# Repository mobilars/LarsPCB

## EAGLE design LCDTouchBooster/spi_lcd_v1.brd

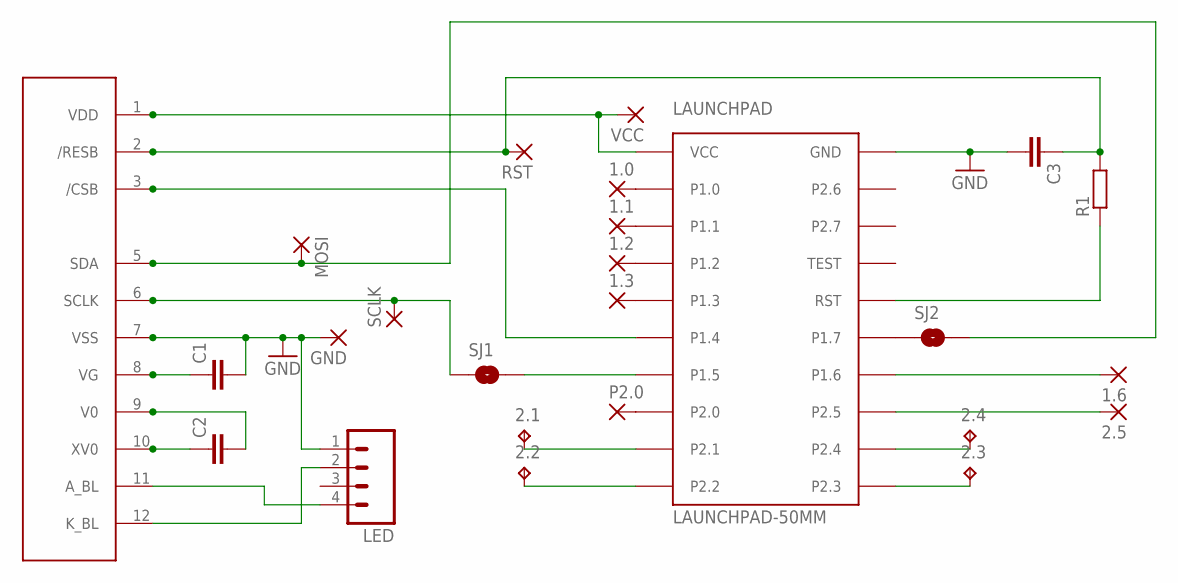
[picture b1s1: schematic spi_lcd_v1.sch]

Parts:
1.0, 1.1, 1.2, 1.3, 1.6, 2.5: 2,15/1,0
2.1, 2.2, 2.3, 2.4: TPTP07R; TP07R
C1, C2, C3: CAP1206; 1206
GND: 2,15/1,0
LAUNCHPAD: LAUNCHPAD-50MM
LED: M04PTH; 1X04
MOSI: 2,15/1,0
P2.0: 2,15/1,0
R1: R-EU_R1206; R1206
RST: 2,15/1,0
SCLK: 2,15/1,0
SJ1, SJ2: SOLDERJUMPERTRACE; SJ_2S-TRACE
U$1: PE9665WRFPE9665WRF-WHOLE; PE9665WRF
VCC: 2,15/1,0

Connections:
GND: C1.2, C3.2, GND.1, LAUNCHPAD.GND, LED.1, U$1.7 (VSS)
unnamed: C2.1, U$1.10 (XV0)
unnamed: C2.2, U$1.9 (V0)
unnamed: C1.1, U$1.8 (VG)
unnamed: 2.5.1, LAUNCHPAD.P2.5
unnamed: C3.1, R1.2, RST.1, U$1.2 (/RESB)
unnamed: 1.0.1, LAUNCHPAD.P1.0
unnamed: SCLK.1, SJ1.1, U$1.6 (SCLK)
unnamed: MOSI.1, SJ2.2, U$1.5 (SDA)
unnamed: LAUNCHPAD.P1.4, U$1.3 (/CSB)
unnamed: LAUNCHPAD.RST, R1.1
unnamed: 1.6.1, LAUNCHPAD.P1.6
unnamed: 1.2.1, LAUNCHPAD.P1.2
unnamed: 2.1.TP, LAUNCHPAD.P2.1
unnamed: 2.2.TP, LAUNCHPAD.P2.2
unnamed: 2.4.TP, LAUNCHPAD.P2.4
unnamed: 2.3.TP, LAUNCHPAD.P2.3
unnamed: 1.3.1, LAUNCHPAD.P1.3
unnamed: LAUNCHPAD.P2.0, P2.0.1
unnamed: 1.1.1, LAUNCHPAD.P1.1
unnamed: LAUNCHPAD.P1.7, SJ2.1
unnamed: LAUNCHPAD.P1.5, SJ1.2
unnamed: LED.2, U$1.12 (K_BL)
unnamed: LED.4, U$1.11 (A_BL)
VDD: LAUNCHPAD.VCC, U$1.1 (VDD), VCC.1

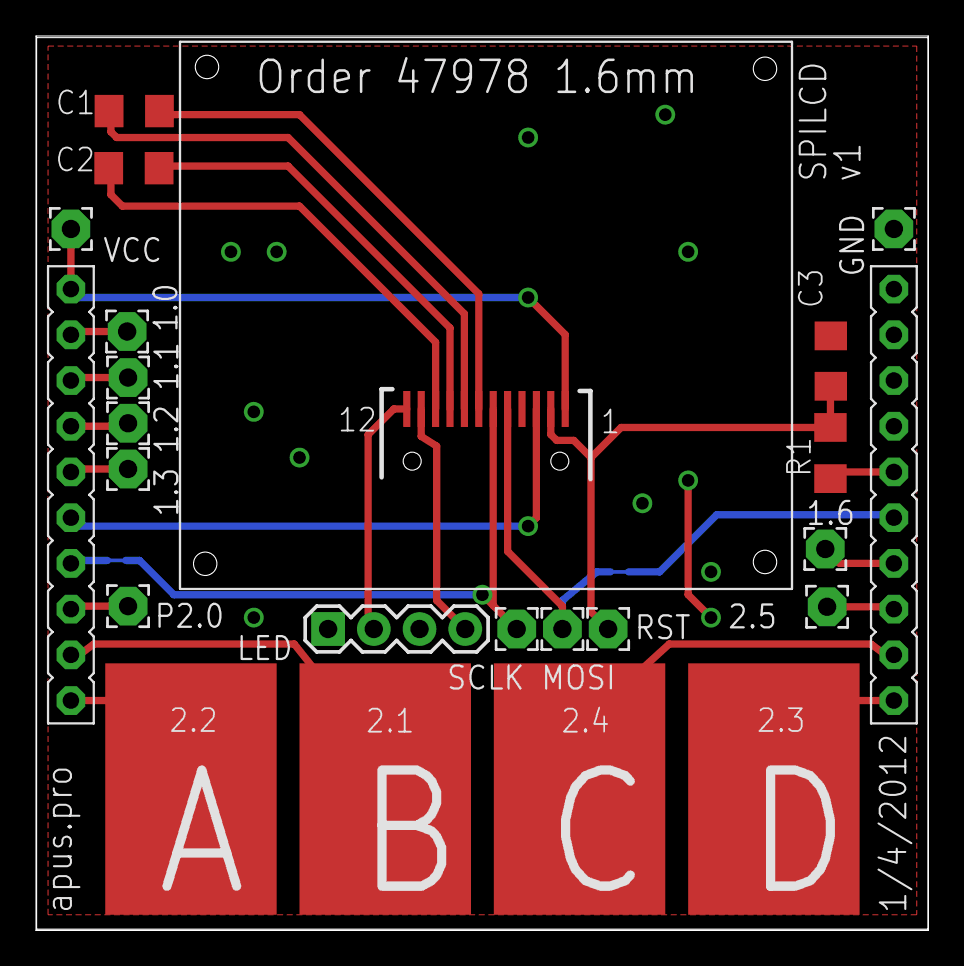
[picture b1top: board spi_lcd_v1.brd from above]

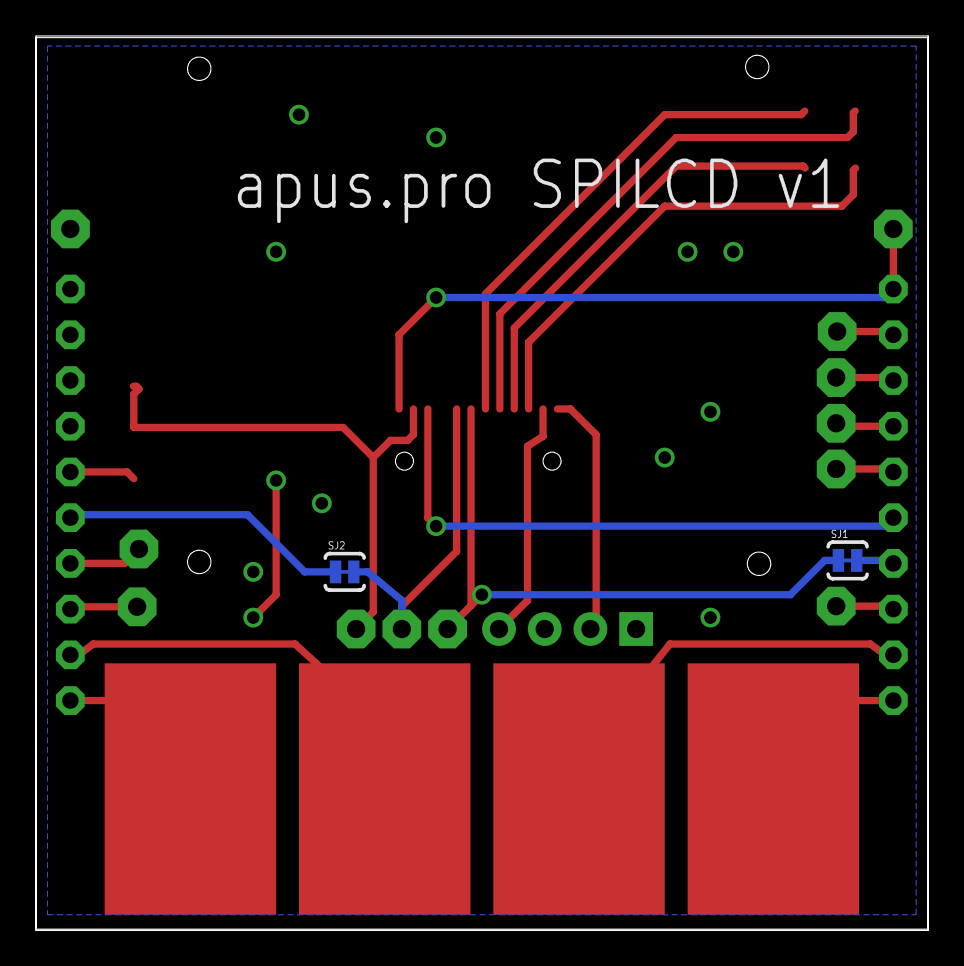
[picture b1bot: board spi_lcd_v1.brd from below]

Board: 2 copper layers, 49.6 x 49.7 mm, 25 parts (2 on the bottom side), 25 nets.

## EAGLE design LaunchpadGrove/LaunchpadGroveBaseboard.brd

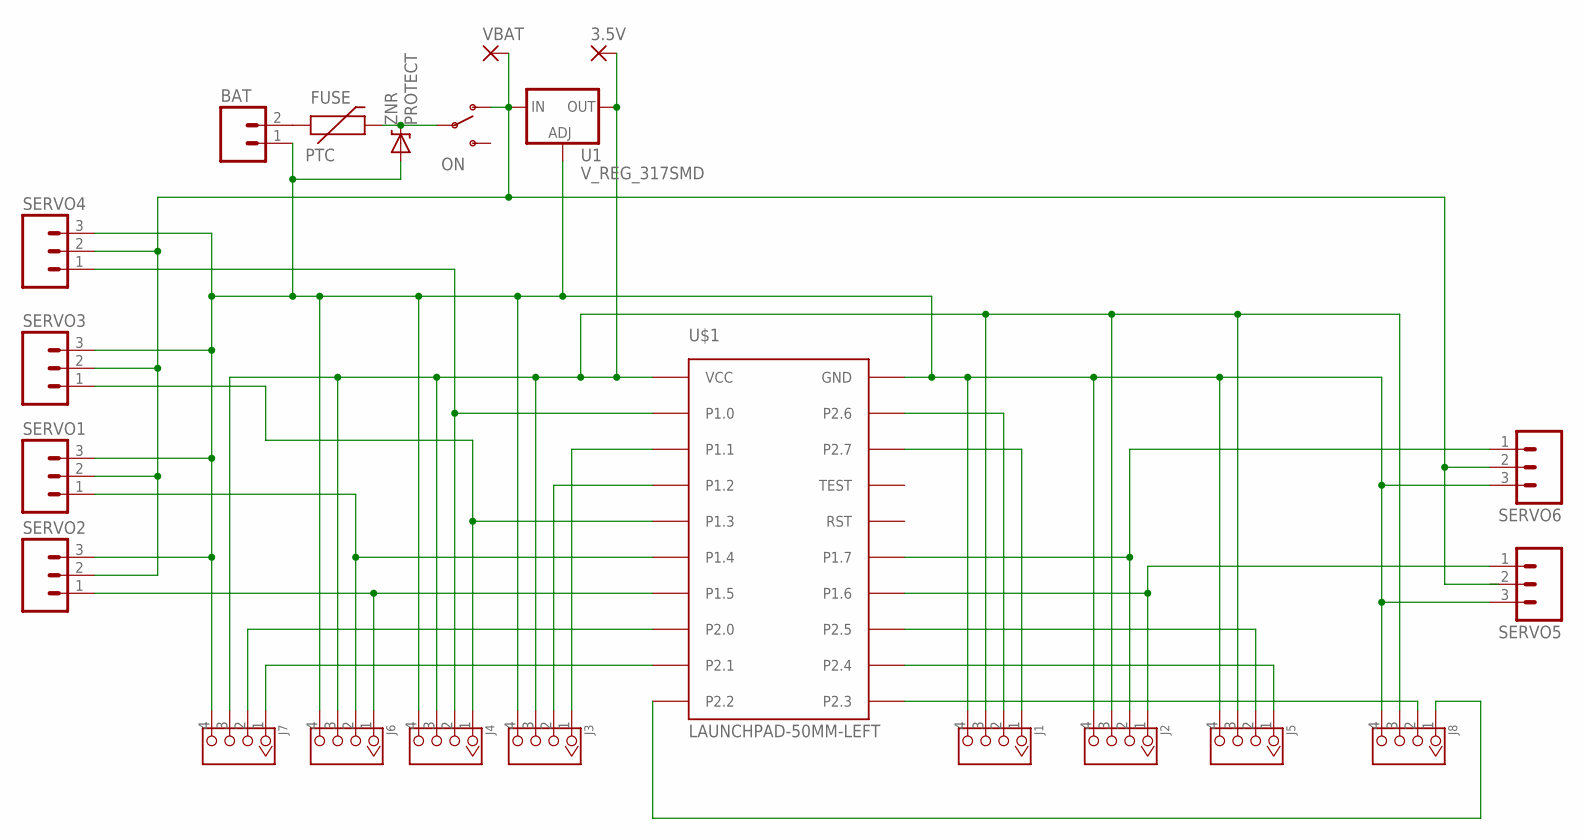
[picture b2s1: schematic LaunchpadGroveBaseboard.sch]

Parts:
3.5V: 2,15/1,0
BAT: M02PTH3; 1X02_LONGPADS
FUSE: PTC
J1, J2, J3, J4, J5, J6, J7, J8: TWIG-4P-2.0-2.0; 4P-2.0
ON: SWITCH-SPSTPTH; SWITCH-SPDT
SERVO1, SERVO2, SERVO3, SERVO4, SERVO5, SERVO6: M03PTH; 1X03
U1: V_REG_317SMD; SOT223
U$1: LAUNCHPAD-50MM-LEFT
VBAT: 2,15/1,0
ZNR: PROTECT; DIODE-ZENER

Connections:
GND: BAT.1, J1.4, J2.4, J3.4, J4.4, J5.4, J6.4, J7.4, J8.4, SERVO1.3, SERVO2.3, SERVO3.3, SERVO4.3, SERVO5.3, SERVO6.3, U1.1 (ADJ), U$1.GND, ZNR.P$2 (A)
unnamed: J3.2, U$1.P1.2
unnamed: BAT.2, FUSE.P$1 (1)
unnamed: J4.2, SERVO4.1, U$1.P1.0
unnamed: J3.1, U$1.P1.1
unnamed: J4.1, SERVO3.1, U$1.P1.3
unnamed: J6.2, SERVO1.1, U$1.P1.4
unnamed: J6.1, SERVO2.1, U$1.P1.5
unnamed: J1.2, U$1.P2.6
unnamed: J1.1, U$1.P2.7
unnamed: J2.2, SERVO6.1, U$1.P1.7
unnamed: J2.1, SERVO5.1, U$1.P1.6
unnamed: J5.2, U$1.P2.5
unnamed: J5.1, U$1.P2.4
unnamed: J7.2, U$1.P2.0
unnamed: FUSE.P$2 (2), ON.2, ZNR.P$1 (C)
unnamed: J8.1, U$1.P2.2
unnamed: J8.2, U$1.P2.3
unnamed: J7.1, U$1.P2.1
VBAT: ON.1 (O), SERVO1.2, SERVO2.2, SERVO3.2, SERVO4.2, SERVO6.2, U1.3 (IN), VBAT.1
VCC: 3.5V.1, J1.3, J2.3, J3.3, J4.3, J5.3, J6.3, J7.3, J8.3, U1.2 (OUT), U$1.VCC

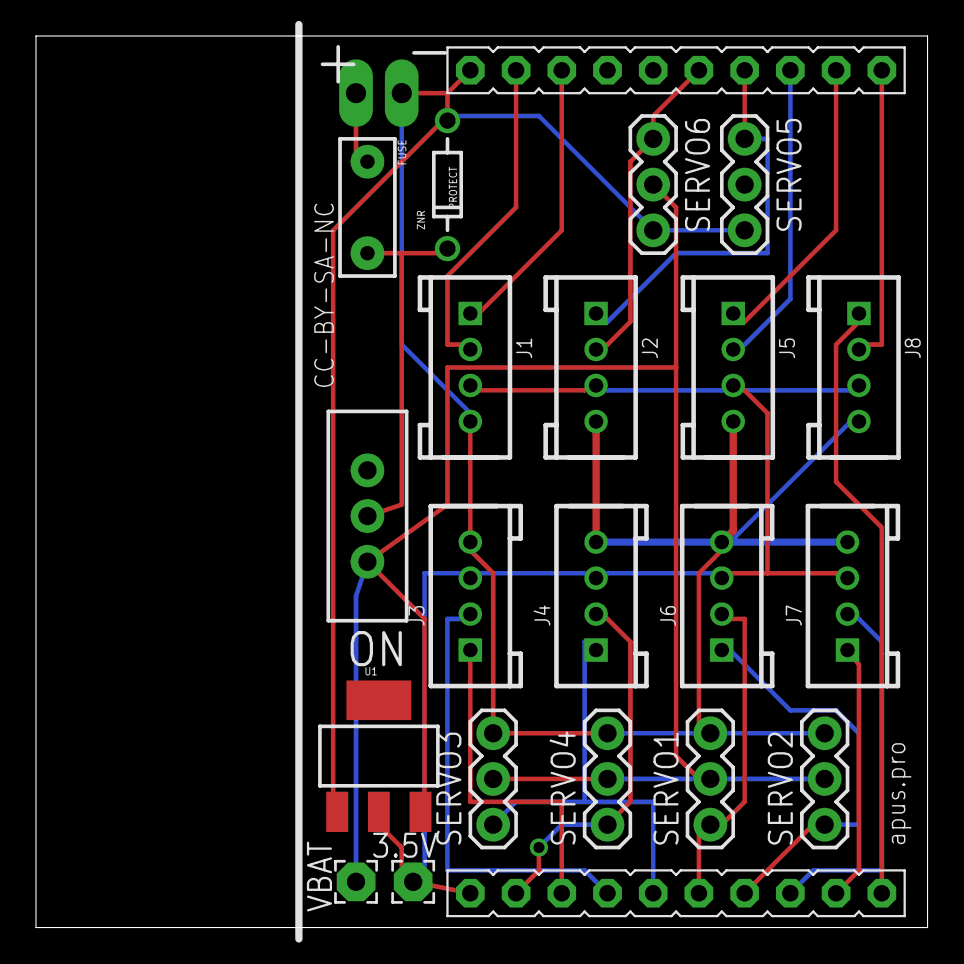
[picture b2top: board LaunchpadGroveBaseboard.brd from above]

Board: 2 copper layers, 49.5 x 49.5 mm, 22 parts (0 on the bottom side), 21 nets.

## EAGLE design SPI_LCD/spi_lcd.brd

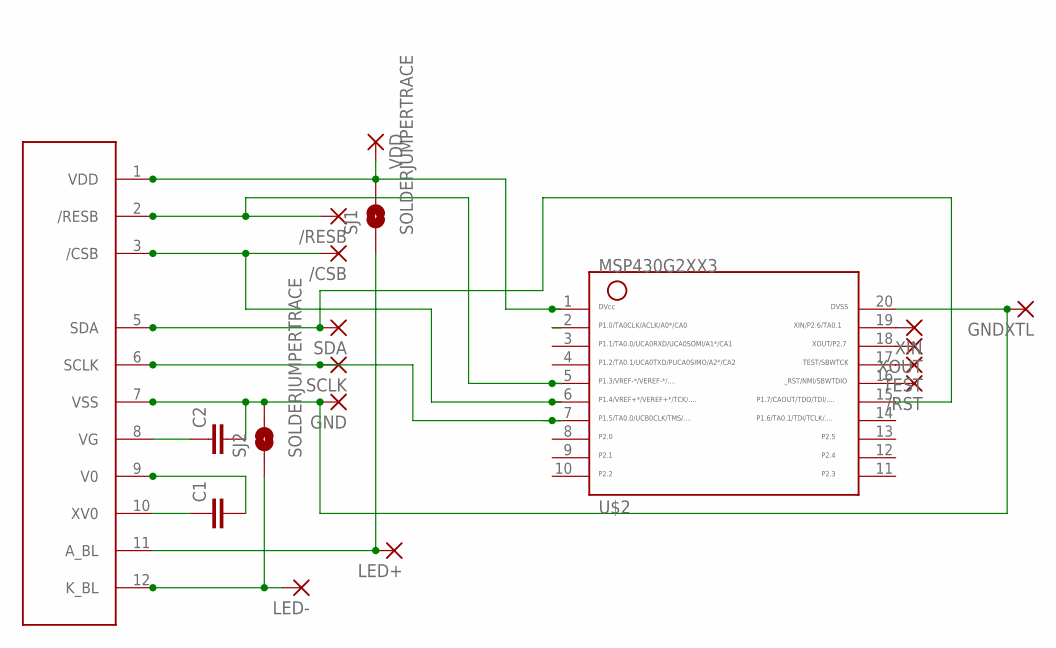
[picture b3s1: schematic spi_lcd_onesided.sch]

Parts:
/CSB: 1,6/0,9
/RESB: 1,6/0,9
/RST: 1,6/0,9
C1, C2: CAP0805; 0805
GND: 1,6/0,9
GNDXTL: SMD2; SMD1,27-2,54
LED+: 1,6/0,9
LED-: 1,6/0,9
SCLK: 1,6/0,9
SDA: 1,6/0,9
SJ1, SJ2: SOLDERJUMPERTRACE; SJ_2S-TRACE
TEST: 1,6/0,9
U$1: PE9665WRFPE9665WRF-WHOLE; PE9665WRF
U$2: G2XX3---PW20; PW20
VDD: 1,6/0,9
XIN: SMD2; SMD1,27-2,54
XOUT: SMD2; SMD1,27-2,54

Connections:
C2: C2.1, U$1.8 (VG)
GND: C2.2, GND.1, GNDXTL.1, SJ2.2, U$1.7 (VSS), U$2.20
unnamed: C1.1, U$1.10 (XV0)
unnamed: C1.2, U$1.9 (V0)
unnamed: U$2.19, XIN.1
unnamed: LED+.1, SJ1.1, U$1.11 (A_BL)
unnamed: LED-.1, SJ2.1, U$1.12 (K_BL)
unnamed: U$2.18, XOUT.1
unnamed: SCLK.1, U$1.6 (SCLK), U$2.7
unnamed: SDA.1, U$1.5 (SDA), U$2.15
unnamed: /CSB.1, U$1.3 (/CSB), U$2.6
unnamed: /RESB.1, U$1.2 (/RESB), U$2.5
unnamed: TEST.1, U$2.17
unnamed: /RST.1, U$2.16
VDD: SJ1.2, U$1.1 (VDD), U$2.1, VDD.1

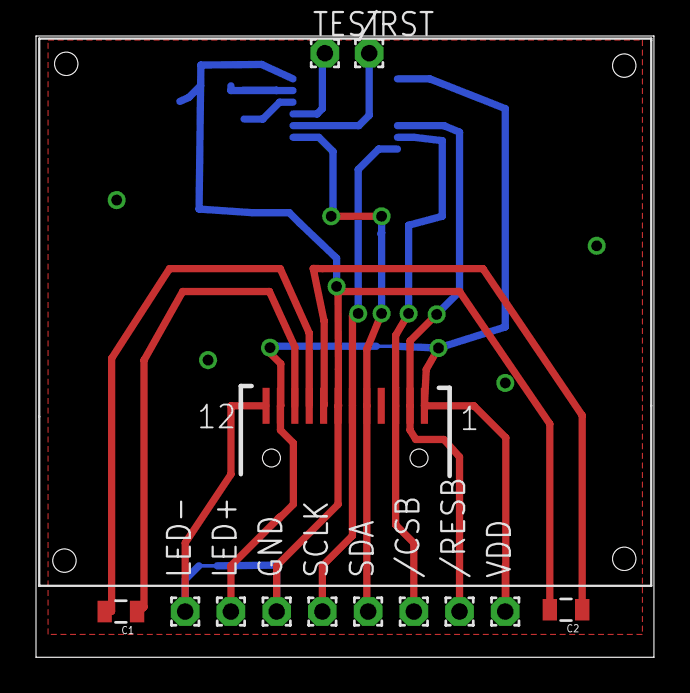
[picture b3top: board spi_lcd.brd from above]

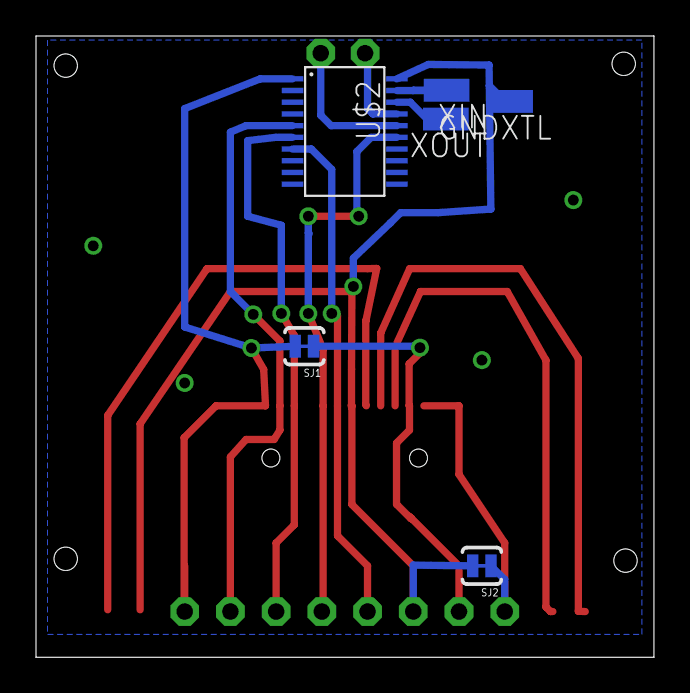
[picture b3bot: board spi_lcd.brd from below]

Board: 2 copper layers, 34.3 x 34.5 mm, 19 parts (6 on the bottom side), 15 nets.

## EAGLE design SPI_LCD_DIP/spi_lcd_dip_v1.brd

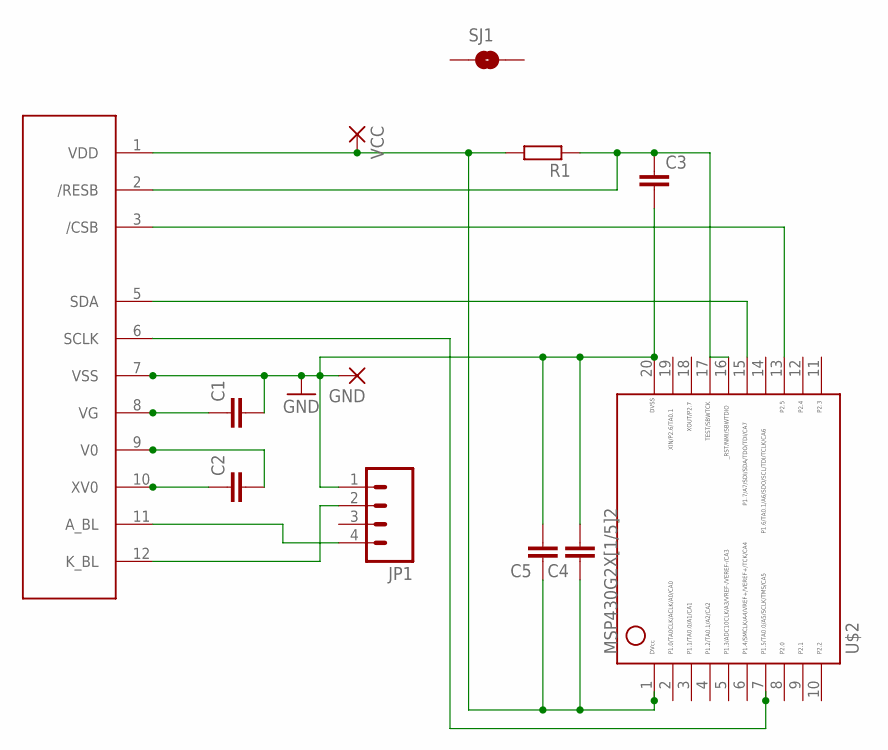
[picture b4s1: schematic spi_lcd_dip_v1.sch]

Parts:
C1, C2, C3, C4, C5: CAP1206; 1206
GND: 2,15/1,0
JP1: M04PTH; 1X04
R1: R-EU_R1206; R1206
SJ1: SOLDERJUMPERTRACE; SJ_2S-TRACE
U$1: PE9665WRFPE9665WRF-WHOLE; PE9665WRF
U$2: G2X[1/5]2---N20; N20
VCC: 2,15/1,0

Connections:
GND: C1.2, C3.2, C4.2, C5.2, GND.1, JP1.1, U$1.7 (VSS), U$2.20
unnamed: C2.1, U$1.10 (XV0)
unnamed: C2.2, U$1.9 (V0)
unnamed: C1.1, U$1.8 (VG)
unnamed: C3.1, R1.1, U$1.2 (/RESB), U$2.16
unnamed: C4.1, C5.1, R1.2, U$1.1 (VDD), U$2.1, VCC.1
unnamed: U$1.5 (SDA), U$2.15
unnamed: U$1.3 (/CSB), U$2.13
unnamed: U$1.6 (SCLK), U$2.7
unnamed: JP1.2, U$1.12 (K_BL)
unnamed: JP1.4, U$1.11 (A_BL)

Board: 2 copper layers, 12 parts (1 on the bottom side), 11 nets, no tracks yet.

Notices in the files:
LaunchpadGrove/LaunchpadGroveBaseboard.brd:
CC-BY-SA-NC
parts and their libraries:
SparkFun: Licensing: CC v3.0 Share-Alike You are welcome to use this library for commercial purposes.
